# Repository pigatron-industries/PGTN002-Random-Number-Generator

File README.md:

# PGTN002 Random Number Generator

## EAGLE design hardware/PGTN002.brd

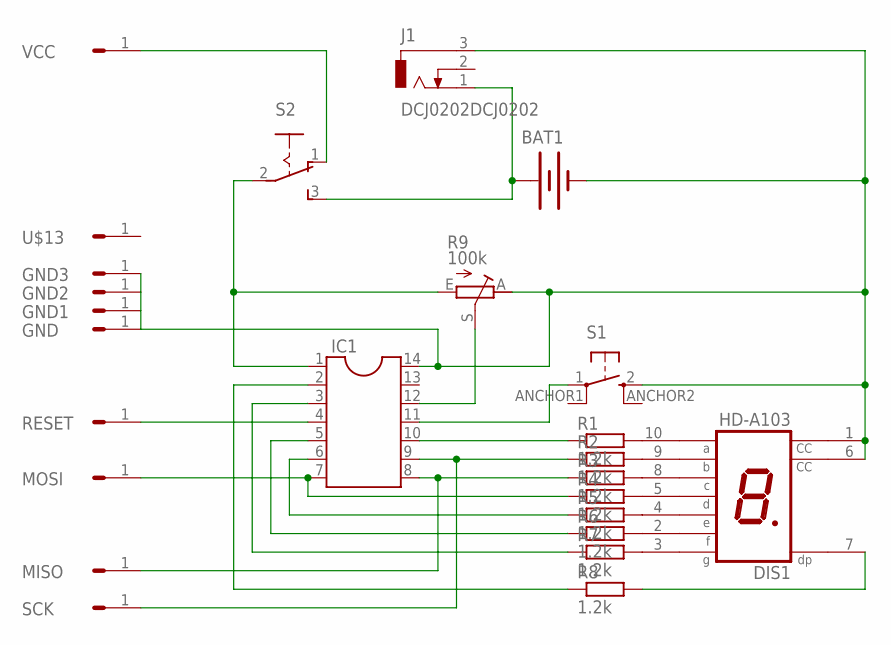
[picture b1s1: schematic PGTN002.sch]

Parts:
BAT1: BATTERY20PTH; BATTCOM_20MM_PTH
DIS1: HD-A103; HDSP-A
GND, GND1, GND2, GND3: HEADER/MALE/01
IC1: DIL14S; SOCKET-14
J1: DCJ0202DCJ0202; DCJ0202
MISO: HEADER/MALE/01
MOSI: HEADER/MALE/01
R1, R2, R3, R4, R5, R6, R7, R8: 1.2k; RESISTOR/7.5
R9: 100k; TRIMMER/LI15
RESET: HEADER/MALE/01
S1: SWITCH_TACTILE; TACTILE-PTH-SIDEEZ
S2: SWITCH_SLIDE
SCK: HEADER/MALE/01
U$13: HEADER/MALE/01
VCC: HEADER/MALE/01

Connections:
GND: BAT1.2 (-), DIS1.1 (CC), DIS1.6 (CC), GND.1, GND1.1, GND2.1, GND3.1, IC1.14, J1.3 (1), R9.A, S1.2 (3)
unnamed: DIS1.10 (A), R1.2
unnamed: DIS1.9 (B), R2.2
unnamed: DIS1.8 (C), R3.2
unnamed: DIS1.5 (D), R4.2
unnamed: DIS1.4 (E), R5.2
unnamed: DIS1.2 (F), R6.2
unnamed: DIS1.3 (G), R7.2
unnamed: DIS1.7 (DP), R8.2
unnamed: IC1.10, R1.1
unnamed: IC1.8, MISO.1, R3.1
unnamed: IC1.9, R2.1, SCK.1
unnamed: IC1.7, MOSI.1, R4.1
unnamed: IC1.6, R5.1
unnamed: IC1.5, R6.1
unnamed: IC1.3, R7.1
unnamed: IC1.2, R8.1
unnamed: IC1.11, S1.1
unnamed: IC1.12, R9.S
unnamed: IC1.1, R9.E, S2.2
unnamed: BAT1.1 (+), J1.1 (3), S2.3 (S)
unnamed: IC1.4, RESET.1
unnamed: S2.1 (O), VCC.1

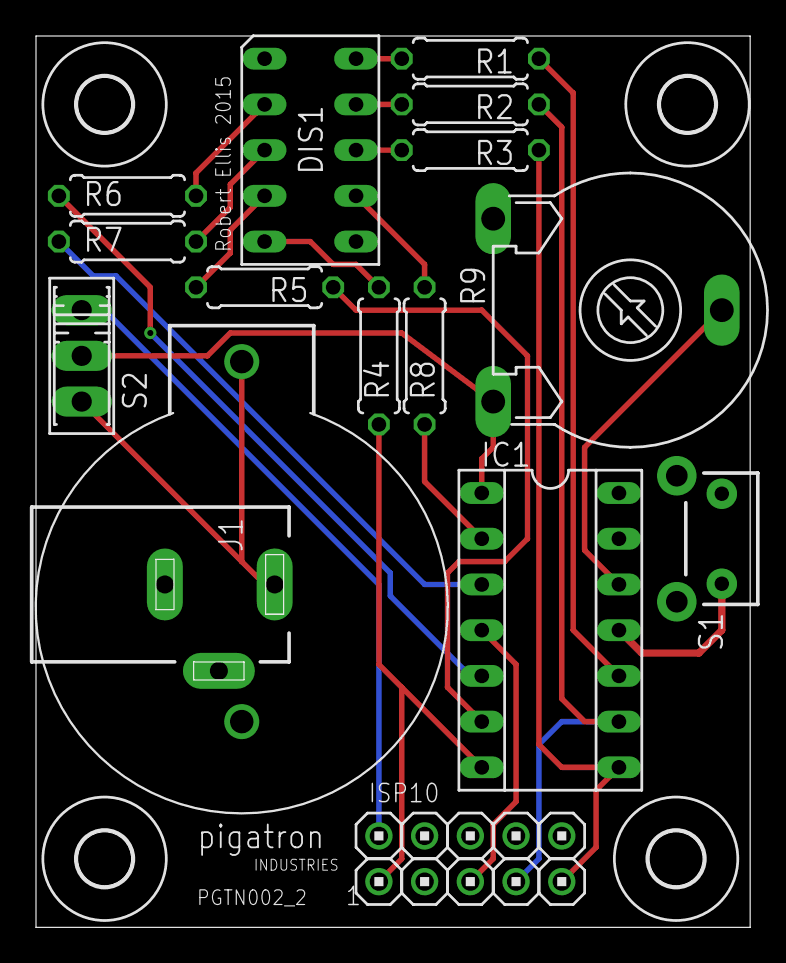
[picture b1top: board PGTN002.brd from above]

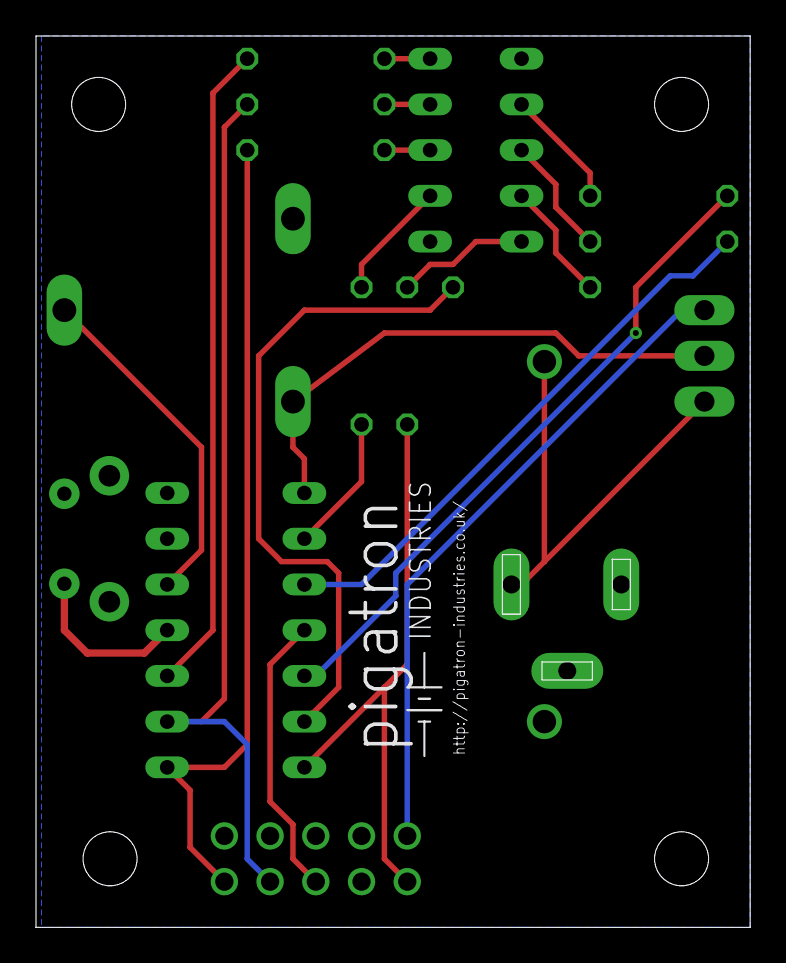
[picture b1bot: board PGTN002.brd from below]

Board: 2 copper layers, 39.7 x 49.5 mm, 31 parts (2 on the bottom side), 23 nets.

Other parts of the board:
U$1, U$2, U$3, U$4: STANDOFF/3.0
U$11: PIGATRON-LOGO
U$12: PIGATRON-WEB

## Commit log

2015-08-11 Fixed MISO and SCK connection between ATTINY44 and ISP10 socket swapped
2015-08-11 Max number now starts at 2. Fixed issue with Arduino random number generator always picking same number after seeding.
